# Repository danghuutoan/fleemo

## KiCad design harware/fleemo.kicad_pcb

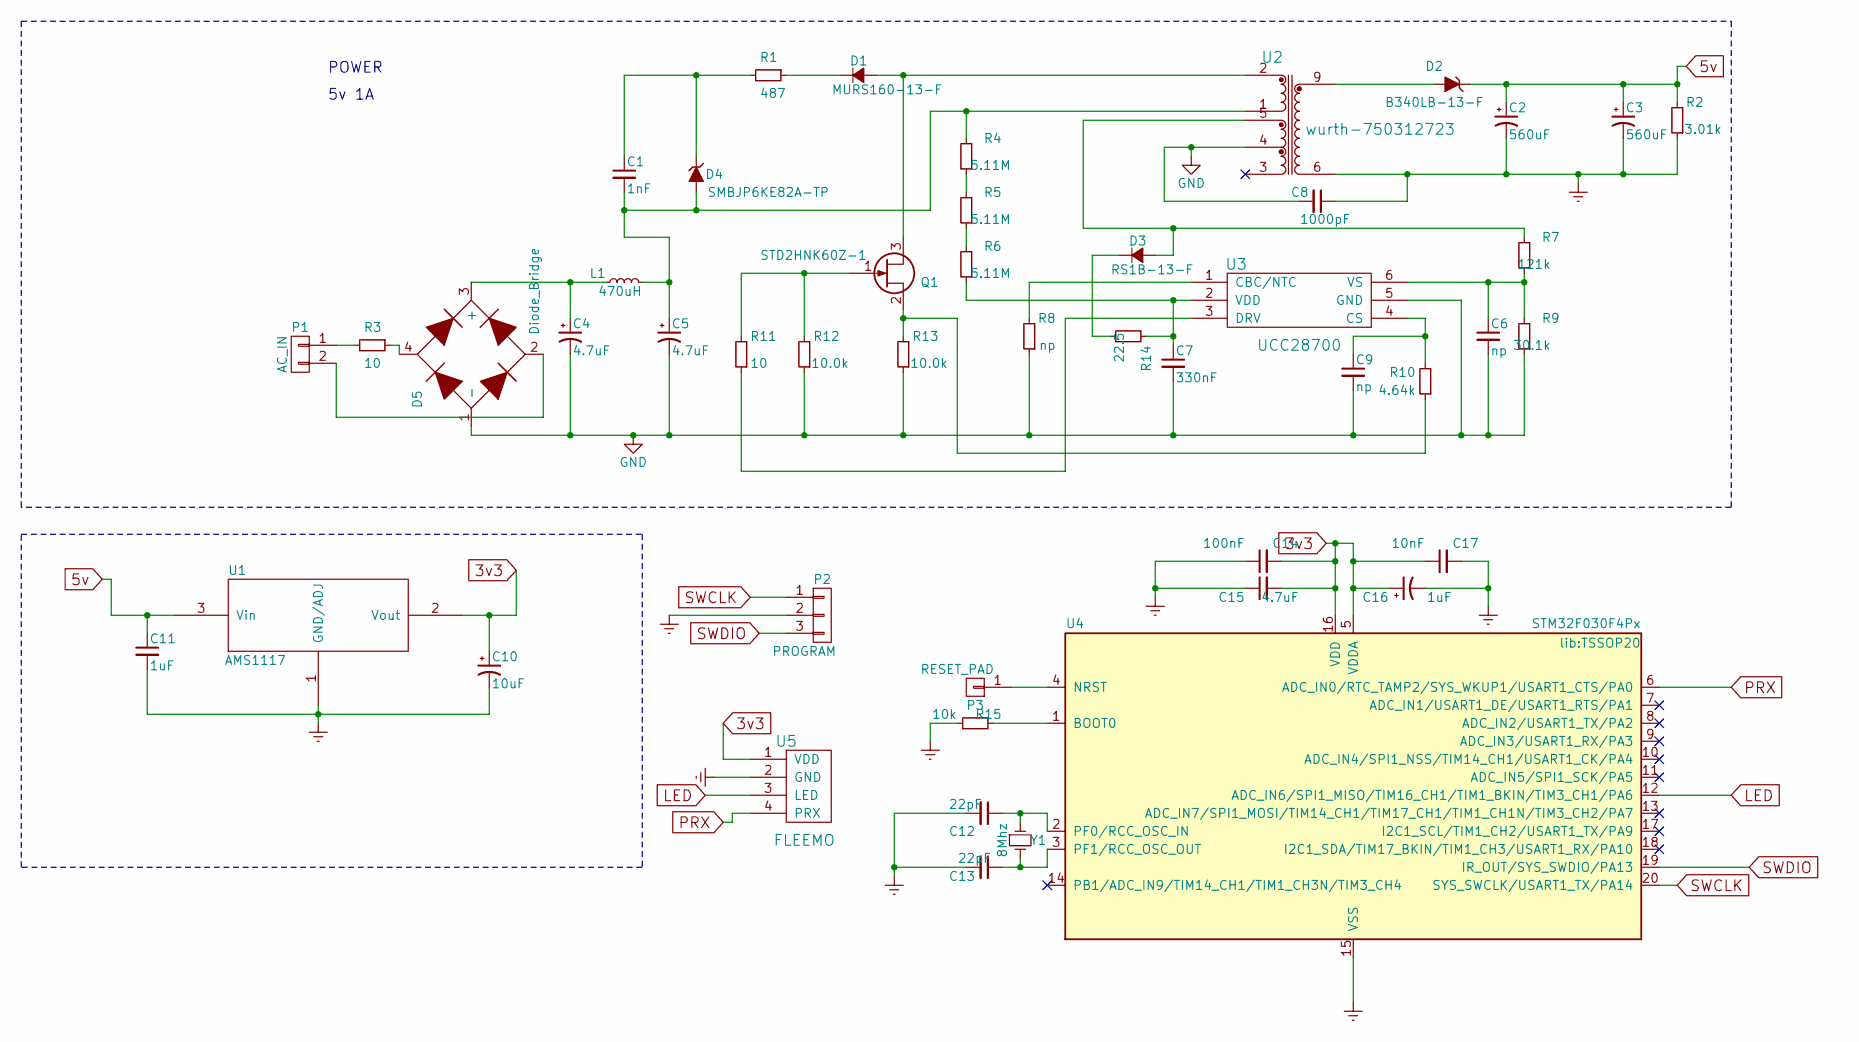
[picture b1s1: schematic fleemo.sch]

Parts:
C1: 1nF; C_1206_HandSoldering
C2, C3: 560uF; C_Radial_D10_L13_P5
C4, C5: 4.7uF; C_Radial_D10_L16_P5
C6, C9: np; C_0805_HandSoldering
C7: 330nF; C_0805_HandSoldering
C8: 1000pF; C_Rect_L13_W4_P10
C10: 10uF; TantalC_SizeA_EIA-3216_HandSoldering
C11: 1uF; C_0805_HandSoldering
C12, C13: 22pF; C_0805_HandSoldering
C14: 100nF; C_0805_HandSoldering
C15: 4.7uF; C_0805_HandSoldering
C16: 1uF; TantalC_SizeA_EIA-3216_HandSoldering
C17: 10nF; C_0805_HandSoldering
D1: MURS160-13-F; Diode_DO-41_SOD81_Horizontal_RM10
D2: B340LB-13-F; SMB_Handsoldering
D3: RS1B-13-F; SMA_Handsoldering
D4: SMBJP6KE82A-TP; SMB_Handsoldering
D5: Diode_Bridge; diode_bridge
L1: 470uH; choke_F_2mm
P1: AC_IN
P2: PROGRAM; Pin_Header_Straight_1x03
P3: RESET_PAD; Pin_Header_Straight_1x01
Q1: STD2HNK60Z-1; TO-251AA
R1: 487; R_0805_HandSoldering
R2: 3.01k; R_0805_HandSoldering
R3: 10; Resistor_Horizontal_RM15mm
R4, R5, R6: 5.11M; R_0805_HandSoldering
R7: 121k; R_0805_HandSoldering
R8: np; R_0805_HandSoldering
R9: 30.1k; R_0805_HandSoldering
R10: 4.64k; R_0805_HandSoldering
R11: 10; R_0805_HandSoldering
R12: 10.0k; R_0805_HandSoldering
R13: 10.0k; R_1206_HandSoldering
R14: 22.5; R_0805_HandSoldering
R15: 10k; R_0805_HandSoldering
U1: AMS1117; SOT-223
U2: wurth-750312723; 750312723
U3: UCC28700; SOT-23-6_Handsoldering
U4: STM32F030F4Px; TSSOP20
U5: FLEEMO; fleemo
Y1: 8Mhz; Crystal_HC49-SD_SMD

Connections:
3v3: C10.1, C14.2, C15.2, C16.1, C17.1, U1.2 (Vout), U4.5 (VDDA), U4.16 (VDD), U5.1 (VDD)
5v: C2.1, C3.1, C11.1, D2.1 (K), R2.2, U1.3 (Vin)
Earth: C2.2, C3.2, C8.1, C10.2, C11.2, C12.2, C13.2, C14.1, C15.1, C16.2, C17.2, P2.2, R2.1, R15.1, U1.1 (GND/ADJ), U2.6, U4.15 (VSS), U5.2 (GND)
GND: C4.2, C5.2, C6.2, C7.2, C8.2, C9.2, D5.1 (-), R8.1, R9.1, R12.1, R13.1, U2.4, U3.5 (GND)
LED: U4.12 (ADC_IN6/SPI1_MISO/TIM16_CH1/TIM1_BKIN/T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), U5.3 (LED)
unnamed: C1.1, D4.1 (K), R1.2
unnamed: C1.2, C5.1, D4.2 (A), L1.2, R4.2, U2.1
unnamed: C4.1, D5.3 (+), L1.1
unnamed: C6.1, R7.1, R9.2, U3.6 (VS)
unnamed: C7.1, R6.1, R14.2, U3.2 (VDD)
unnamed: C9.1, R10.2, U3.4 (CS)
unnamed: C12.1, U4.2 (PF0/RCC_OSC_IN), Y1.1
unnamed: C13.1, U4.3 (PF1/RCC_OSC_OUT), Y1.2
unnamed: D1.1 (K), R1.1
unnamed: D1.2 (A), Q1.3 (S), U2.2
unnamed: D2.2 (A), U2.9
unnamed: D3.1 (K), R14.1
unnamed: D3.2 (A), R7.2, U2.5
unnamed: D5.2, P1.2
unnamed: D5.4, R3.1
unnamed: P1.1, R3.2
unnamed: P3.1, U4.4 (NRST)
unnamed: Q1.1 (G), R11.2, R12.2
unnamed: Q1.2 (D), R10.1, R13.2
unnamed: R4.1, R5.2
unnamed: R5.1, R6.2
unnamed: R8.2, U3.1 (CBC/NTC)
unnamed: R11.1, U3.3 (DRV)
unnamed: R15.2, U4.1 (BOOT0)
PRX: U4.6 (ADC_IN0/RTC_TAMP2/SYS_WKUP1/USART1_CTS/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), U5.4 (PRX)
SWCLK: P2.1, U4.20 (SYS_SWCLK/USART1_TX/PA14)
SWDIO: P2.3, U4.19 (IR_OUT/SYS_SWDIO/PA13)

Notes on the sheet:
POWER
5v 1A

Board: 2 copper layers, 48 parts (0 on the bottom side), 32 nets, no tracks yet.

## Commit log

2016-06-28 first time commit
2016-06-28 modify stack size and flash
2016-06-29 add adc code, printf function
2016-07-12 add hardware
2016-07-14 modify sch
2016-07-15 add value of the components
2016-07-19 update sch
2016-07-19 add transformer symbol
2016-07-19 edit transformer symbol
2016-07-19 finish powe section
2016-07-20 add 5v label
2016-07-21 add stepdown circuit
2016-07-22 add mcu circuit
2016-07-22 change bypass cap value
2016-07-25 add footprint
2016-07-26 add some more footprint
2016-07-27 adding more footprint
2016-07-28 create pcb
